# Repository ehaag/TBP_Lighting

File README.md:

# TBP_Lighting
**Ceremony lighting for Tau Beta Pi**

This repo holds the documentation for the Tau Beta Pi ceremony lighting revamp created by Erik Haag in Fall 2021. The main purpose of the project was to modernize some of the less-than-savory, officially sponsored hacks that were used to make the original system "safe". Main highlights include:
  * Moving from a mains-powered incandescent lamp to an LED lamp powered from low voltage DC
  * Improving the durability of the system through improved connectors, strain reliefs, and other parts
  * Custom PCB including overvoltage, reverse voltage, and overcurrent protection

The content here consists primarily of two sections. First, the user manual (i.e., the Wiki in the tab above) contains the basic information needed to operate the lighting system. Honestly, it's really pretty simple. There are lots of pictures. Don't be afraid. The other section pertains to the custom PCB that was designed for this project. It includes a schematic, a bill of materials, an assembly drawing, the KiCad project files, and the Gerbers for the board itself.

Finally, for any questions or concerns not explicitly addressed by the documents contained in this repository, please feel free to use the issue tracker associated with this repository. I have also included my U of M email address on the inside of the control unit's cover, in case I happen to miss anything here.

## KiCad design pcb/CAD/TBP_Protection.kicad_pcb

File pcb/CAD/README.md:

CAD files for the protection board. Please see the associated [Wiki page](https://github.com/ehaag/TBP_Lighting/wiki/CAD).

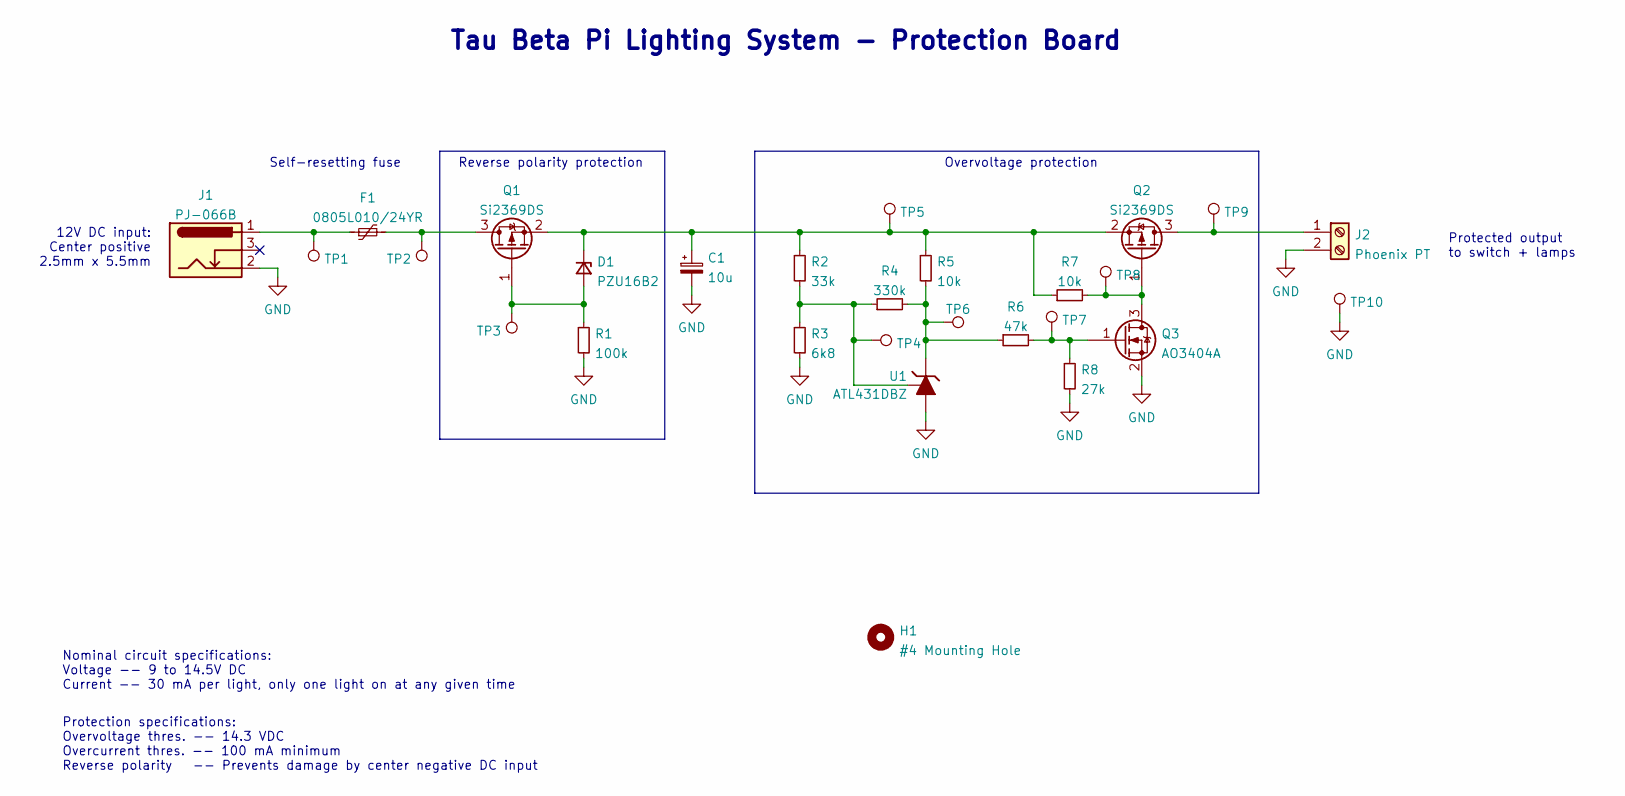
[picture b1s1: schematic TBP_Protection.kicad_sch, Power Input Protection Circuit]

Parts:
C1: 10u; CP_EIA-3528-12_Kemet-T
D1: ‎PZU16B2; D_SOD-323F
F1: ‎0805L010/24YR‎; Fuse_0805_2012Metric
H1: #4 Mounting Hole; MountingHole_3.5mm
J1: PJ-066B; BarrelJack_CUI_PJ-066A
J2: Phoenix PT; TerminalBlock_Phoenix_MKDS-1,5-2-5.08_1x02_P5.08mm_Horizont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
Q1, Q2: Si2369DS; SOT-23
Q3: AO3404A; SOT-23
R1: 100k; R_0603_1608Metric
R2: 33k; R_0603_1608Metric
R3: 6k8; R_0603_1608Metric
R4: 330k; R_0603_1608Metric
R5, R7: 10k; R_0603_1608Metric
R6: 47k; R_0603_1608Metric
R8: 27k; R_0603_1608Metric
TP1, TP2, TP3, TP4, TP5, TP6, TP7, TP8, TP9, TP10: TestPoint_Small; TestPoint_Pad_D1.5mm
U1: ATL431DBZ; SOT-23

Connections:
GND: C1.2, J1.2, J2.2, Q3.2 (S), R1.2, R3.2, R8.2, TP10.1, U1.3 (A)
unnamed: C1.1, D1.1 (K), Q1.2 (S), Q2.2 (S), R2.1, R5.1, R7.1, TP5.1
unnamed: D1.2 (A), Q1.1 (G), R1.1, TP3.1
unnamed: F1.1, J1.1, TP1.1
unnamed: F1.2, Q1.3 (D), TP2.1
unnamed: J2.1, Q2.3 (D), TP9.1
unnamed: Q2.1 (G), Q3.3 (D), R7.2, TP8.1
unnamed: Q3.1 (G), R6.2, R8.1, TP7.1
unnamed: R2.2, R3.1, R4.1, TP4.1, U1.2 (REF)
unnamed: R4.2, R5.2, R6.1, TP6.1, U1.1 (K)

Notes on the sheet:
Overvoltage protection
12V DC input: Center positive 2.5mm x 5.5mm
Nominal circuit specifications: Voltage -- 9 to 14.5V DC Current -- 30 mA per light, only one light on at any given time
Protected output to switch + lamps
Reverse polarity protection
Protection specifications: Overvoltage thres. -- 14.3 VDC Overcurrent thres. -- 100 mA minimum Reverse polarity -- Prevents damage by center negative DC input
Tau Beta Pi Lighting System - Protection Board
Self-resetting fuse

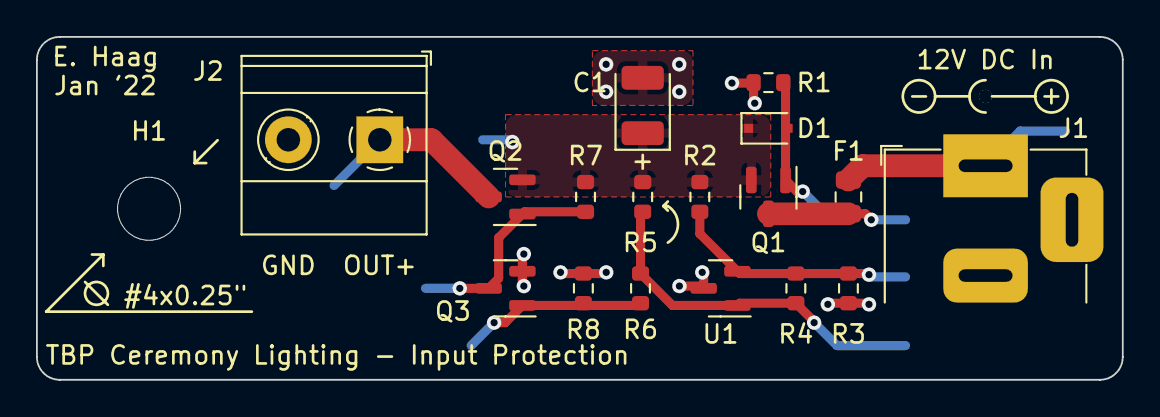
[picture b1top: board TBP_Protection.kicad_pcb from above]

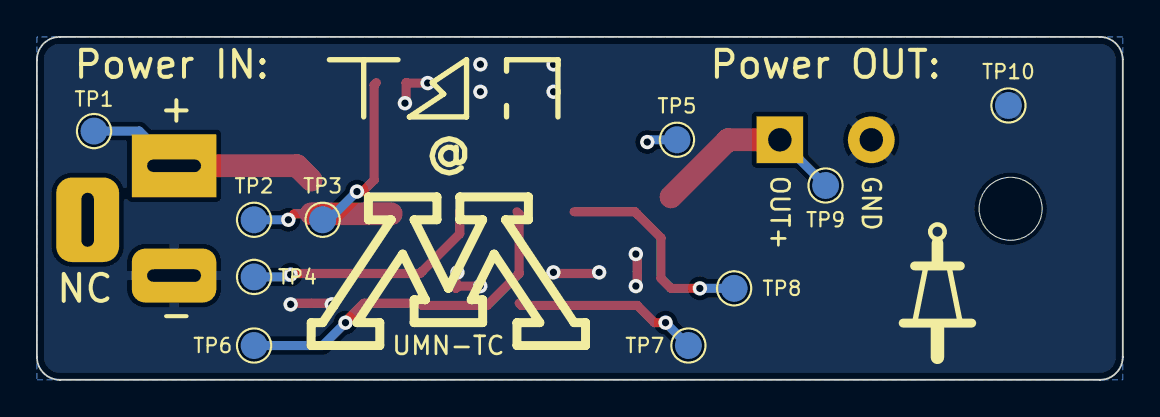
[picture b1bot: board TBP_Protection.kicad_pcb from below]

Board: 2 copper layers, 60.3 x 19.1 mm, 28 parts (10 on the bottom side), 10 nets.

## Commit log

2022-03-11 Final draft of README.md
    Wrote up the readme.
2022-03-12 Added images for wiki
2022-03-12 Update to clarify Wiki as user manual
2022-03-12 Removed dummy
2022-03-12 Added PCB files
2022-03-12 Added BOM
2022-03-13 Remove KiCad project file
2022-03-13 Added SPICE sim
